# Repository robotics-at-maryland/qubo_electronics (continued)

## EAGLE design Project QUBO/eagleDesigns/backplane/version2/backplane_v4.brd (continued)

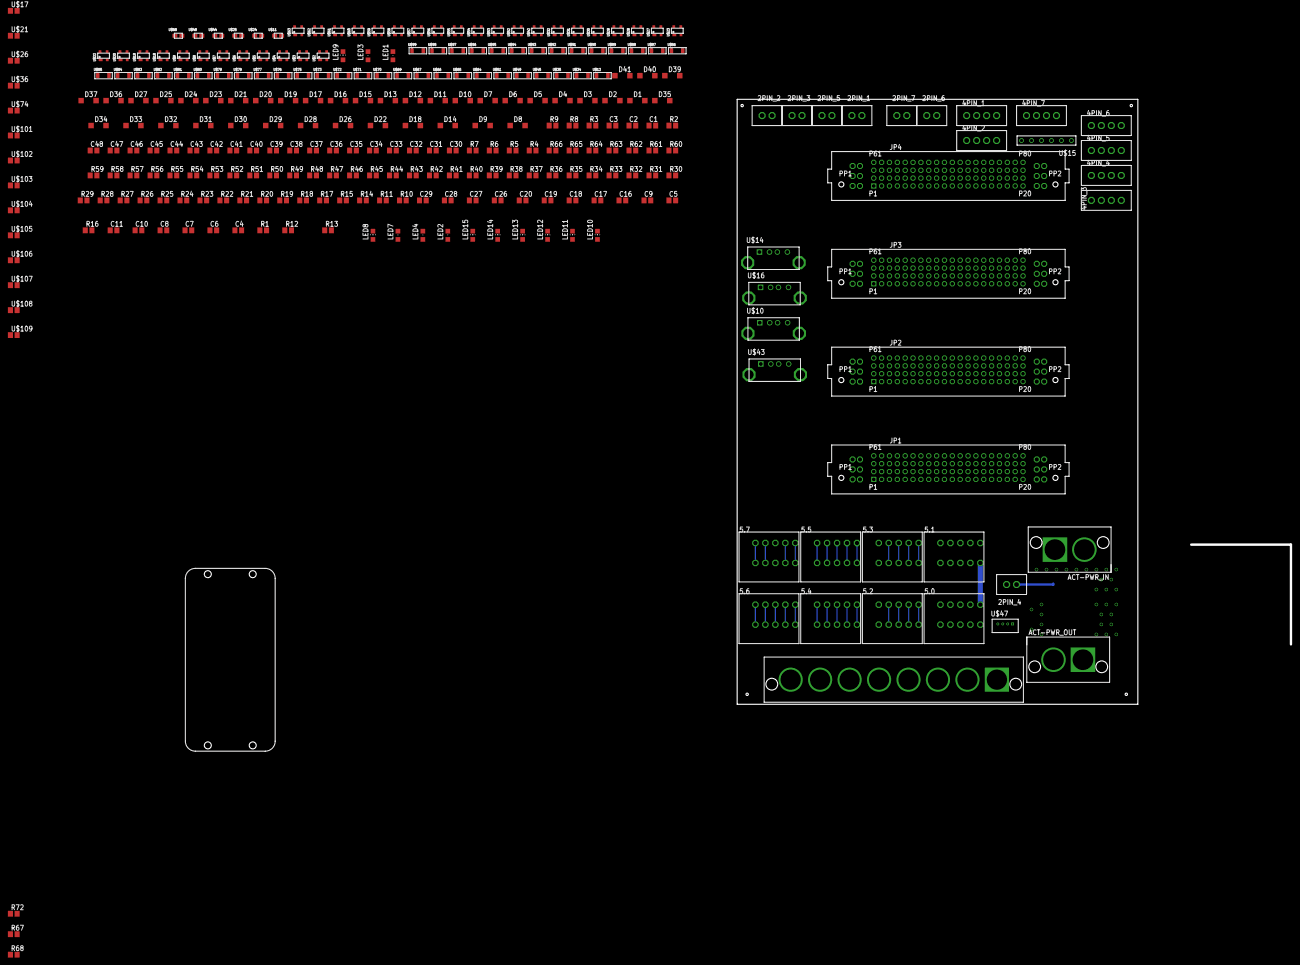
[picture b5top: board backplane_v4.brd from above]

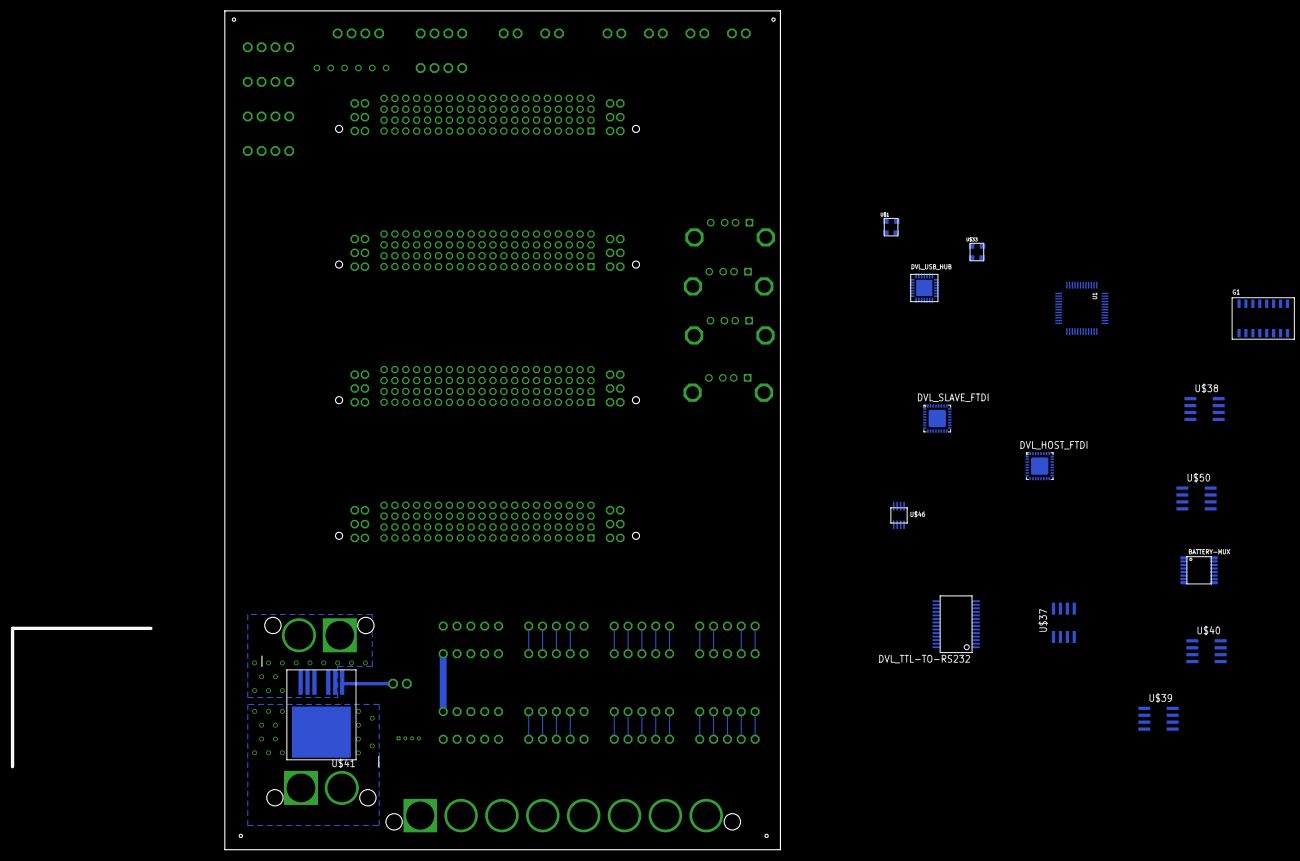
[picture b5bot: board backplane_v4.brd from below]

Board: 6 copper layers, 141.0 x 154.0 mm, 305 parts (16 on the bottom side), 197 nets.

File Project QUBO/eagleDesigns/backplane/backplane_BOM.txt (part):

Partlist exported from C:/Users/Ben/Documents/Dropbox/Documents/UMD/R@M/RAM Tran Electronics_2016/qubo_electronics.git/Project QUBO/eagleDesigns/backplane/version2/backplane_v4.sch at Tue, 2/7/2017 3:39 PM

Part             Value                     Device                    Package             Description                                                                               MF MPN     OC_FARNELL OC_NEWARK
2PIN_1           CPU_USB_HUB               KK254_VERT_2PIN22-29-2021 KK254_VERT_2PIN     KK® 254 Wire-to-Board Header, Vertical, with Friction Lock, 2 Circuits, Gold (Au) Plating                                
2PIN_2           CPU_USB_AHRS              KK254_VERT_2PIN22-29-2021 KK254_VERT_2PIN     KK® 254 Wire-to-Board Header, Vertical, with Friction Lock, 2 Circuits, Gold (Au) Plating                                
2PIN_3           CPU_USB_IMU               KK254_VERT_2PIN22-29-2021 KK254_VERT_2PIN     KK® 254 Wire-to-Board Header, Vertical, with Friction Lock, 2 Circuits, Gold (Au) Plating                                
2PIN_4           Magnetic Reed Switch plug KK254_VERT_2PIN22-29-2021 KK254_VERT_2PIN     KK® 254 Wire-to-Board Header, Vertical, with Friction Lock, 2 Circuits, Gold (Au) Plating                                
2PIN_5           CPU_USB_DVL               KK254_VERT_2PIN22-29-2021 KK254_VERT_2PIN     KK® 254 Wire-to-Board Header, Vertical, with Friction Lock, 2 Circuits, Gold (Au) Plating                                
2PIN_6           CPU_I2C_1                 KK254_VERT_2PIN22-29-2021 KK254_VERT_2PIN     KK® 254 Wire-to-Board Header, Vertical, with Friction Lock, 2 Circuits, Gold (Au) Plating                                
2PIN_7           CPU_CAN                   KK254_VERT_2PIN22-29-2021 KK254_VERT_2PIN     KK® 254 Wire-to-Board Header, Vertical, with Friction Lock, 2 Circuits, Gold (Au) Plating                                
4PIN_1           CPU_RS232_MCU             KK254_VERT_4PIN22-29-2041 KK254_VERT_4PIN     KK® 254 Wire-to-Board Header, Vertical, with Friction Lock, 4 Circuits, Gold (Au) Plating                                
4PIN_2           CPU_RS232_Flex            KK254_VERT_4PIN22-29-2041 KK254_VERT_4PIN     KK® 254 Wire-to-Board Header, Vertical, with Friction Lock, 4 Circuits, Gold (Au) Plating                                
4PIN_3           CPU_PWR1                  KK254_VERT_4PIN22-29-2041 KK254_VERT_4PIN     KK® 254 Wire-to-Board Header, Vertical, with Friction Lock, 4 Circuits, Gold (Au) Plating                                
4PIN_4           CPU_PWR2                  KK254_VERT_4PIN22-29-2041 KK254_VERT_4PIN     KK® 254 Wire-to-Board Header, Vertical, with Friction Lock, 4 Circuits, Gold (Au) Plating                                
4PIN_5           CPU_GND1                  KK254_VERT_4PIN22-29-2041 KK254_VERT_4PIN     KK® 254 Wire-to-Board Header, Vertical, with Friction Lock, 4 Circuits, Gold (Au) Plating                                
4PIN_6           CPU_GND2                  KK254_VERT_4PIN22-29-2041 KK254_VERT_4PIN     KK® 254 Wire-to-Board Header, Vertical, with Friction Lock, 4 Circuits, Gold (Au) Plating                                
4PIN_7           CPU_SPI                   KK254_VERT_4PIN22-29-2041 KK254_VERT_4PIN     KK® 254 Wire-to-Board Header, Vertical, with Friction Lock, 4 Circuits, Gold (Au) Plating                                
5.0              M250_5PIN                 M250_5PIN                 M205_5PIN           5-pin Eurostyle Terminal Block                                                                                           
5.1              M250_5PIN                 M250_5PIN                 M205_5PIN           5-pin Eurostyle Terminal Block                                                                                           
5.2              M250_5PIN                 M250_5PIN                 M205_5PIN           5-pin Eurostyle Terminal Block                                                                                           
5.3              M250_5PIN                 M250_5PIN                 M205_5PIN           5-pin Eurostyle Terminal Block                                                                                           
5.4              M250_5PIN                 M250_5PIN                 M205_5PIN           5-pin Eurostyle Terminal Block                                                                                           
5.5              M250_5PIN                 M250_5PIN                 M205_5PIN           5-pin Eurostyle Terminal Block                                                                                           
5.6              M250_5PIN                 M250_5PIN                 M205_5PIN           5-pin Eurostyle Terminal Block                                                                                           
5.7              M250_5PIN                 M250_5PIN                 M205_5PIN           5-pin Eurostyle Terminal Block                                                                                           
ACT-PWR_IN       SUPERSABRE_2CIRCUIT       SUPERSABRE_2CIRCUIT       SUPERSABRE_2CIRCUIT Molex SuperSabre                                                                                                         
ACT-PWR_OUT      SUPERSABRE_2CIRCUIT       SUPERSABRE_2CIRCUIT       SUPERSABRE_2CIRCUIT Molex SuperSabre                                                                                                         
BATTERY-MUX      PCA9546APW                PCA9546APW                TSSOP16             NXP 1:4 I2C Multiplexer                                                                                                  
C1               22p                       C-USC0805                 C0805               CAPACITOR, American symbol                                                                                               
C2               22p                       C-USC0805                 C0805               CAPACITOR, American symbol                                                                                               
C3               22p                       C-USC0805                 C0805               CAPACITOR, American symbol                                                                                               
C4               100n                      C-USC0805                 C0805               CAPACITOR, American symbol                                                                                               
C5               4.7u                      C-USC0805                 C0805               CAPACITOR, American symbol                                                                                               
C6               100n                      C-USC0805                 C0805               CAPACITOR, American symbol                                                                                               
C7               100n                      C-USC0805                 C0805               CAPACITOR, American symbol                                                                                               
C8               100n                      C-USC0805                 C0805               CAPACITOR, American symbol                                                                                               
C9               4.7u                      C-USC0805                 C0805               CAPACITOR, American symbol                                                                                               
C10              100n                      C-USC0805                 C0805               CAPACITOR, American symbol                                                                                               
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
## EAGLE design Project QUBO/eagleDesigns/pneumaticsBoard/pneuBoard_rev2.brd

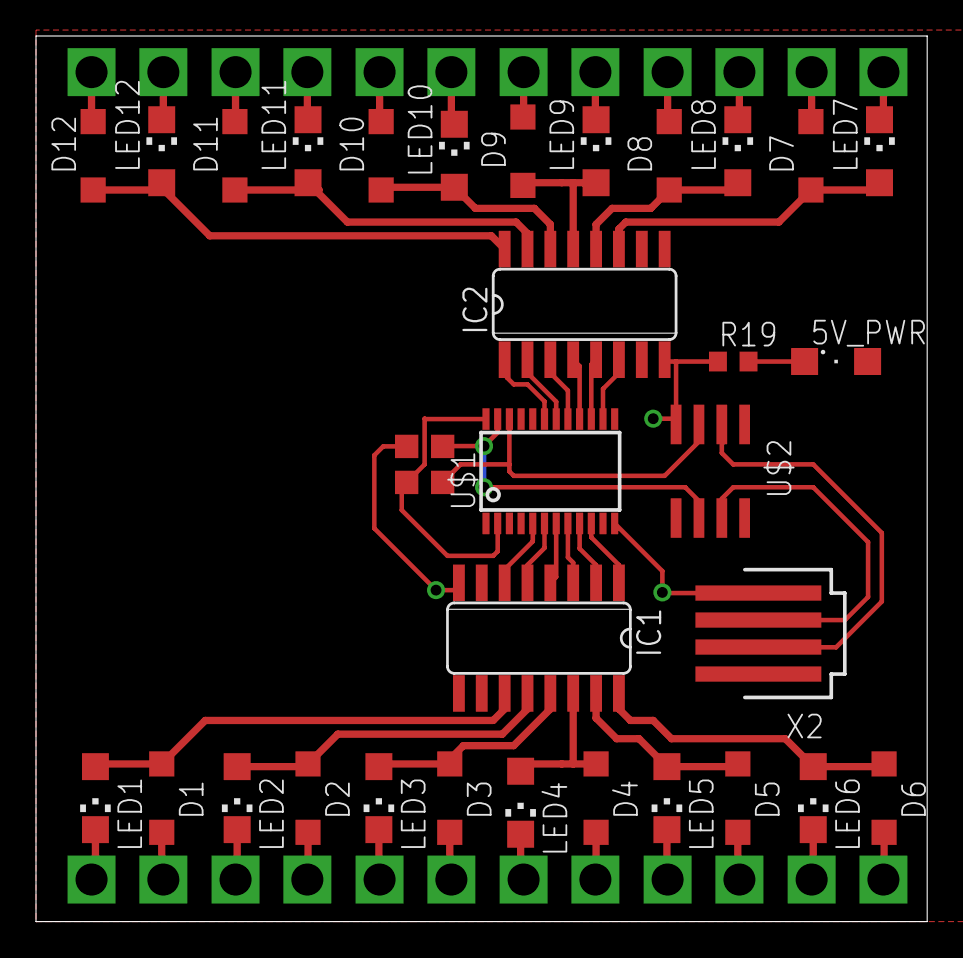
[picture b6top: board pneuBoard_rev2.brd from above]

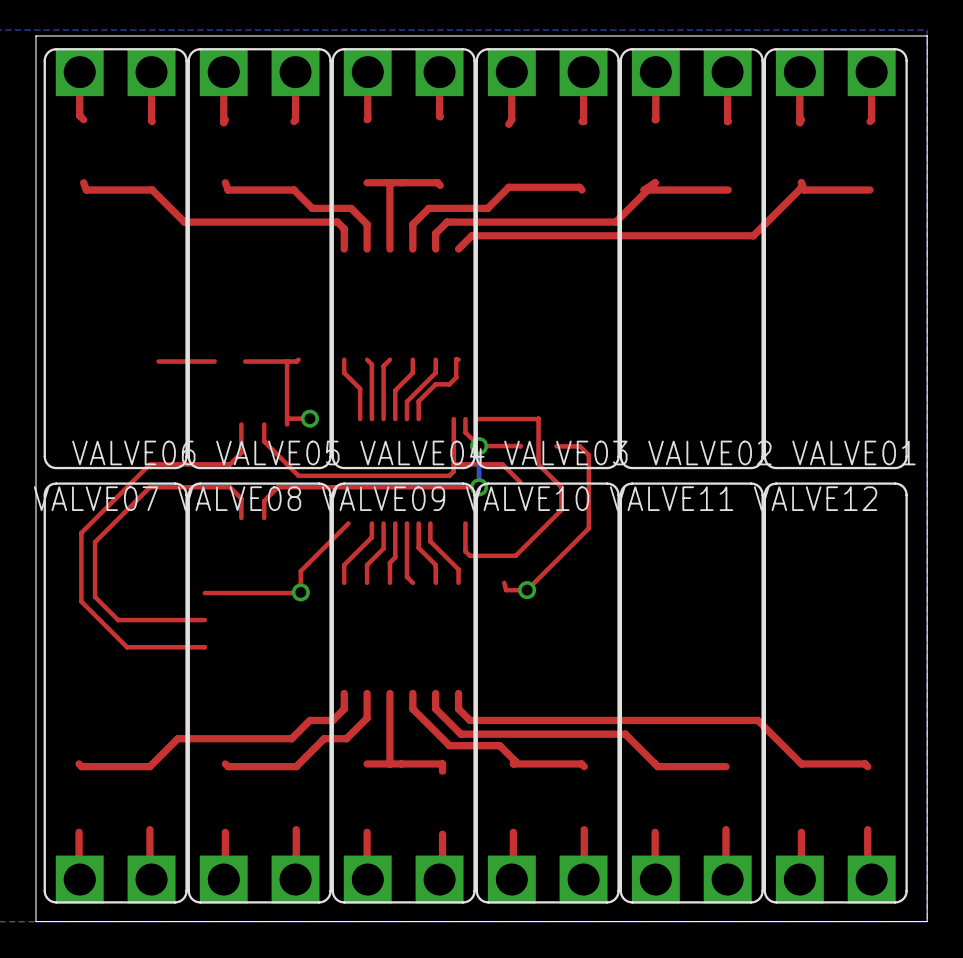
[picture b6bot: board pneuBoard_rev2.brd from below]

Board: 2 copper layers, 49.5 x 49.2 mm, 44 parts (12 on the bottom side), 43 nets.

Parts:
5V_PWR: SML1206
D1, D2, D3, D4, D5, D6, D7, D8, D9, D10, D11, D12: SOD123
IC1, IC2: ULN2001AD; SO16
LED1, LED2, LED3, LED4, LED5, LED6, LED7, LED8, LED9, LED10, LED11, LED12: CHIPLED_1206
R19: 1k; R0603
U$1: PCF8575C; PW_R-PDSO-G24
U$2: P82B715; SO8
U$3: MS5837-30BA
VALVE01, VALVE02, VALVE03, VALVE04, VALVE05, VALVE06, VALVE07, VALVE08, VALVE09, VALVE10, VALVE11, VALVE12: X-5-XX-L-F; X-SERIES
X2: 87438-04

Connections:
5V: 5V_PWR.A, IC1.9, IC2.9, U$1.2, U$1.3, U$1.21, U$1.24, U$2.8, U$3.2, X2.1
5V_LED: 5V_PWR.C, R19.2
GND: D1.A, D2.A, D3.A, D4.A, D5.A, D6.A, D7.A, D8.A, D9.A, D10.A, D11.A, D12.A, IC1.8, IC2.8, R19.1, U$1.12, U$2.4, U$3.1, VALVE01.P2, VALVE02.P2, VALVE03.P2, VALVE04.P2, VALVE05.P2, VALVE06.P2, VALVE07.P2, VALVE08.P2, VALVE09.P2, VALVE10.P2, VALVE11.P2, VALVE12.P2, X2.4
unnamed: LED1.C, VALVE01.P1
unnamed: LED3.C, VALVE03.P1
unnamed: LED4.C, VALVE04.P1
unnamed: LED5.C, VALVE05.P1
unnamed: LED6.C, VALVE06.P1
unnamed: LED9.C, VALVE09.P1
unnamed: LED2.C, VALVE02.P1
unnamed: LED8.C, VALVE08.P1
unnamed: LED7.C, VALVE07.P1
unnamed: LED10.C, VALVE10.P1
unnamed: LED11.C, VALVE11.P1
unnamed: LED12.C, VALVE12.P1
P01: IC1.6, U$1.5
P01_BUF: D1.C, IC1.11, LED1.A
P02: IC1.5, U$1.6
P02_BUF: D2.C, IC1.12, LED2.A
P03: IC1.4, U$1.7
P03_BUF: D3.C, IC1.13, LED3.A
P04: IC1.3, U$1.8
P04_BUF: D4.C, IC1.14, LED4.A
P05: IC1.2, U$1.9
P05_BUF: D5.C, IC1.15, LED5.A
P06: IC1.1, U$1.10
P06_BUF: D6.C, IC1.16, LED6.A
P11: IC2.6, U$1.14
P11_BUF: D7.C, IC2.11, LED7.A
P12: IC2.5, U$1.15
P12_BUF: D8.C, IC2.12, LED8.A
P13: IC2.4, U$1.16
P13_BUF: D9.C, IC2.13, LED9.A
P14: IC2.3, U$1.17
P14_BUF: D10.C, IC2.14, LED10.A
P15: IC2.2, U$1.18
P15_BUF: D11.C, IC2.15, LED11.A
P16: IC2.1, U$1.19
P16_BUF: D12.C, IC2.16, LED12.A
SCL: U$1.22, U$2.3, U$3.3
SCL_BUF: U$2.2, X2.2
SDA: U$1.23, U$2.6, U$3.4
SDA_BUF: U$2.7, X2.3

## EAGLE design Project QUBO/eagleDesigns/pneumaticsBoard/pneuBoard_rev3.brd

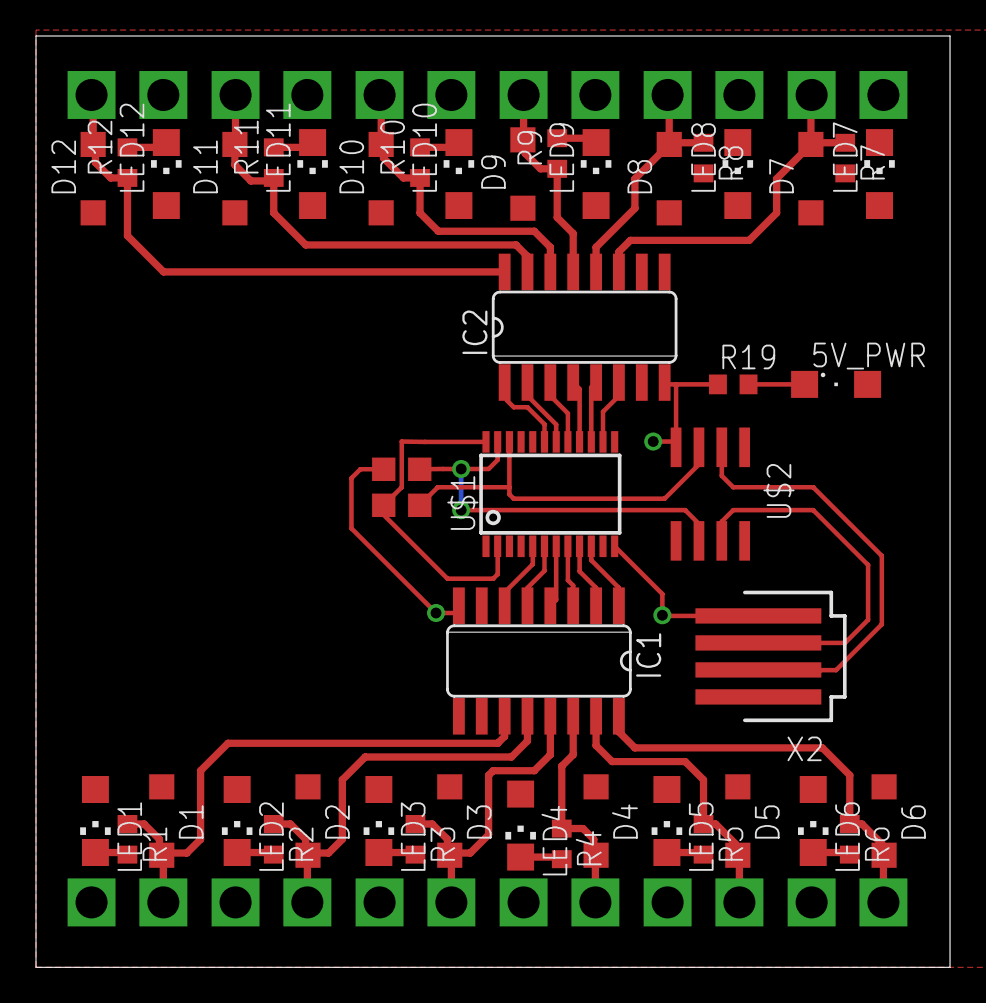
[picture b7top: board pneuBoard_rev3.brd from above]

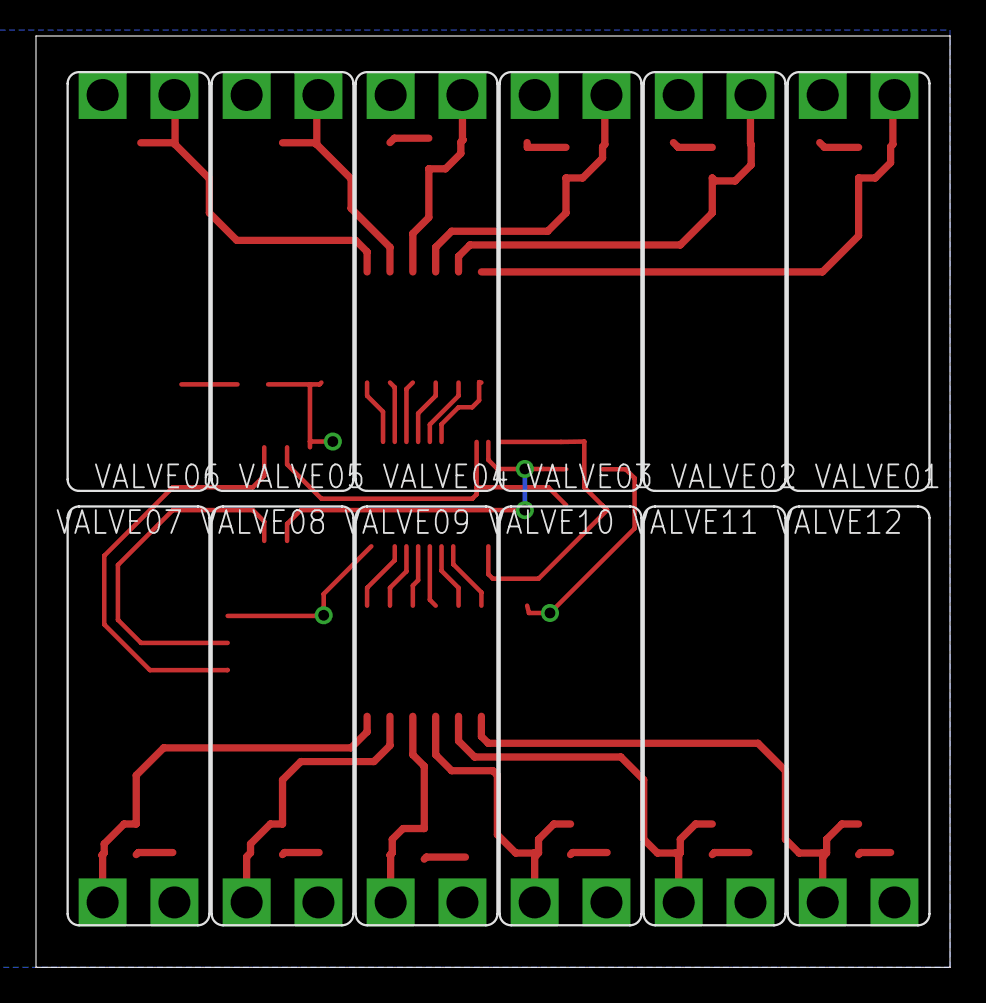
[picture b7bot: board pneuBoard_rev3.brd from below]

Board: 2 copper layers, 50.8 x 51.7 mm, 56 parts (12 on the bottom side), 43 nets.

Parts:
5V_PWR: SML1206
D1, D2, D3, D4, D5, D6, D7, D8, D9, D10, D11, D12: SOD123
IC1, IC2: ULN2001AD; SO16
LED1, LED2, LED3, LED4, LED5, LED6, LED7, LED8, LED9, LED10, LED11, LED12: CHIPLED_1206
R1, R2, R3, R4, R5, R6, R7, R8, R9, R10, R11, R12: R0603
R19: 1k; R0603
U$1: PCF8575C; PW_R-PDSO-G24
U$2: P82B715; SO8
U$3: MS5837-30BA
VALVE01, VALVE02, VALVE03, VALVE04, VALVE05, VALVE06, VALVE07, VALVE08, VALVE09, VALVE10, VALVE11, VALVE12: X-5-XX-L-F; X-SERIES
X2: 87438-04

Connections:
5V: 5V_PWR.A, D1.C, D2.C, D3.C, D4.C, D5.C, D6.C, D7.C, D8.C, D9.C, D10.C, D11.C, D12.C, IC1.9, IC2.9, LED1.A, LED2.A, LED3.A, LED4.A, LED5.A, LED6.A, LED7.A, LED8.A, LED9.A, LED10.A, LED11.A, LED12.A, U$1.2, U$1.3, U$1.21, U$1.24, U$2.8, U$3.2, VALVE01.P1, VALVE02.P1, VALVE03.P1, VALVE04.P1, VALVE05.P1, VALVE06.P1, VALVE07.P1, VALVE08.P1, VALVE09.P1, VALVE10.P1, VALVE11.P1, VALVE12.P1, X2.1
5V_LED: 5V_PWR.C, R19.2
GND: IC1.8, IC2.8, R19.1, U$1.12, U$2.4, U$3.1, X2.4
unnamed: LED4.C, R4.2
unnamed: LED5.C, R5.2
unnamed: LED6.C, R6.2
unnamed: LED1.C, R1.2
unnamed: LED2.C, R2.2
unnamed: LED3.C, R3.2
unnamed: LED7.C, R7.2
unnamed: LED8.C, R8.2
unnamed: LED9.C, R9.2
unnamed: LED10.C, R10.2
unnamed: LED11.C, R11.2
unnamed: LED12.C, R12.2
P01: IC1.6, U$1.5
P01_BUF: D1.A, IC1.11, R1.1, VALVE01.P2
P02: IC1.5, U$1.6
P02_BUF: D2.A, IC1.12, R2.1, VALVE02.P2
P03: IC1.4, U$1.7
P03_BUF: D3.A, IC1.13, R3.1, VALVE03.P2
P04: IC1.3, U$1.8
P04_BUF: D4.A, IC1.14, R4.1, VALVE04.P2
P05: IC1.2, U$1.9
P05_BUF: D5.A, IC1.15, R5.1, VALVE05.P2
P06: IC1.1, U$1.10
P06_BUF: D6.A, IC1.16, R6.1, VALVE06.P2
P11: IC2.6, U$1.14
P11_BUF: D7.A, IC2.11, R7.1, VALVE07.P2
P12: IC2.5, U$1.15
P12_BUF: D8.A, IC2.12, R8.1, VALVE08.P2
P13: IC2.4, U$1.16
P13_BUF: D9.A, IC2.13, R9.1, VALVE09.P2
P14: IC2.3, U$1.17
P14_BUF: D10.A, IC2.14, R10.1, VALVE10.P2
P15: IC2.2, U$1.18
P15_BUF: D11.A, IC2.15, R11.1, VALVE11.P2
P16: IC2.1, U$1.19
P16_BUF: D12.A, IC2.16, R12.1, VALVE12.P2
SCL: U$1.22, U$2.3, U$3.3
SCL_BUF: U$2.2, X2.2
SDA: U$1.23, U$2.6, U$3.4
SDA_BUF: U$2.7, X2.3

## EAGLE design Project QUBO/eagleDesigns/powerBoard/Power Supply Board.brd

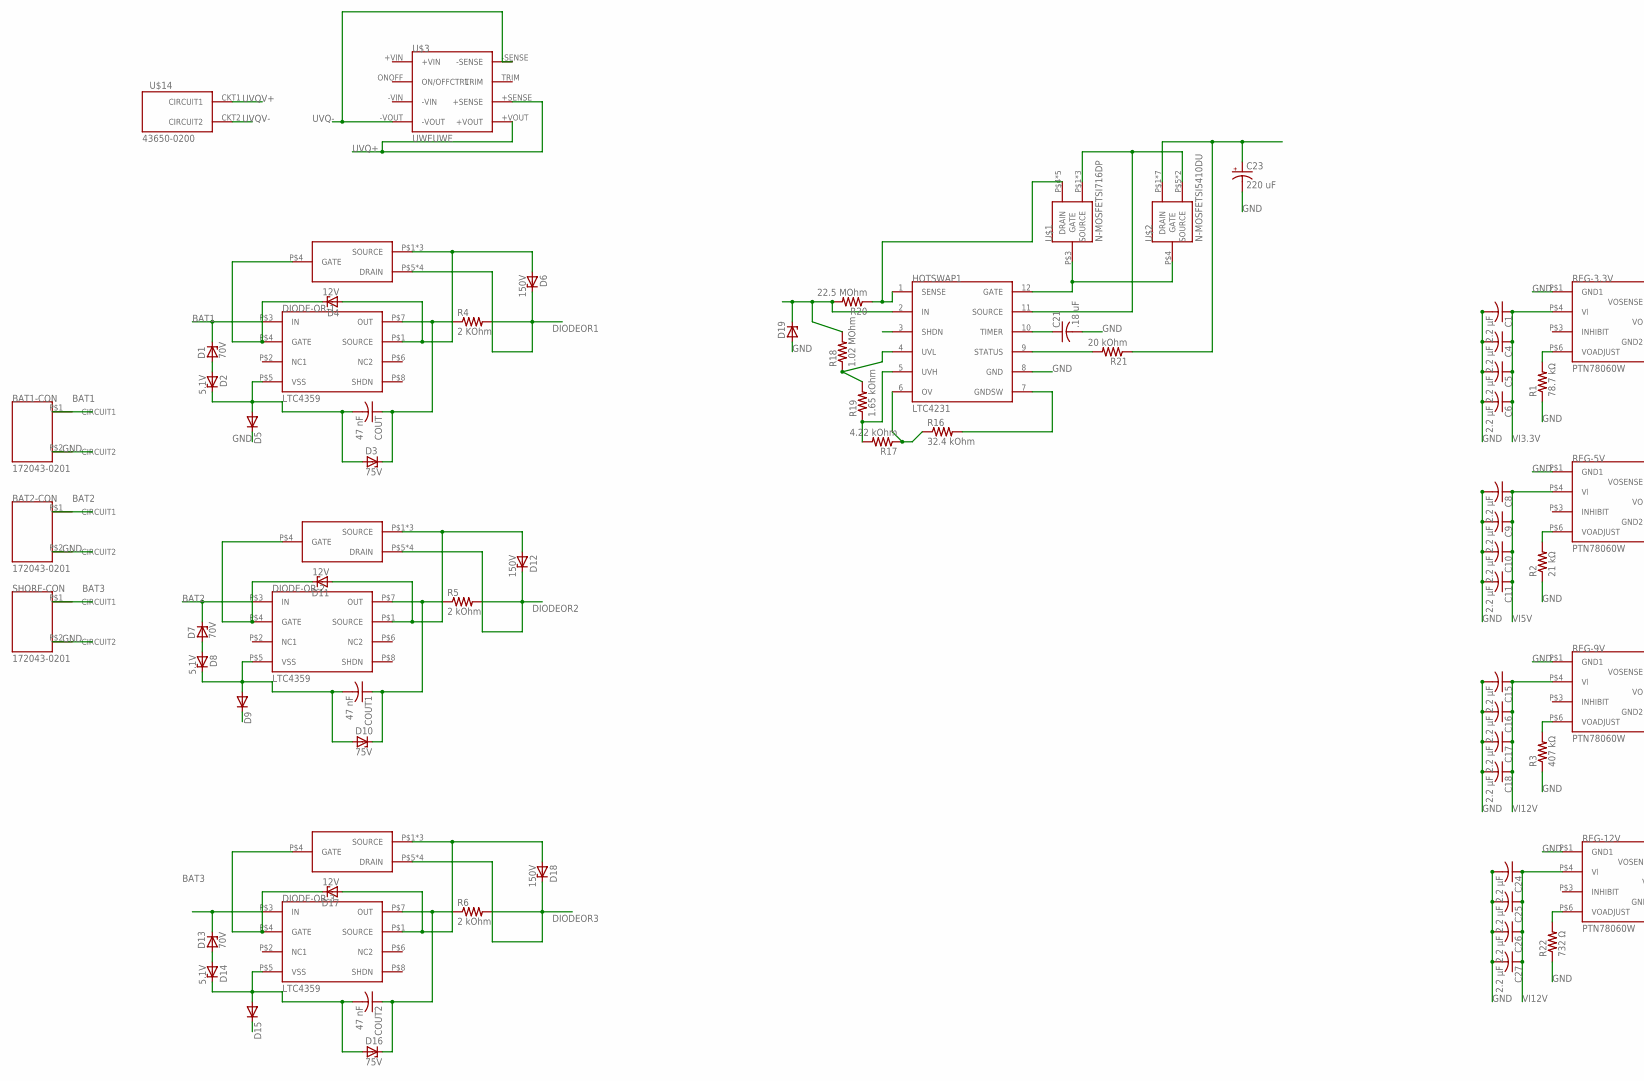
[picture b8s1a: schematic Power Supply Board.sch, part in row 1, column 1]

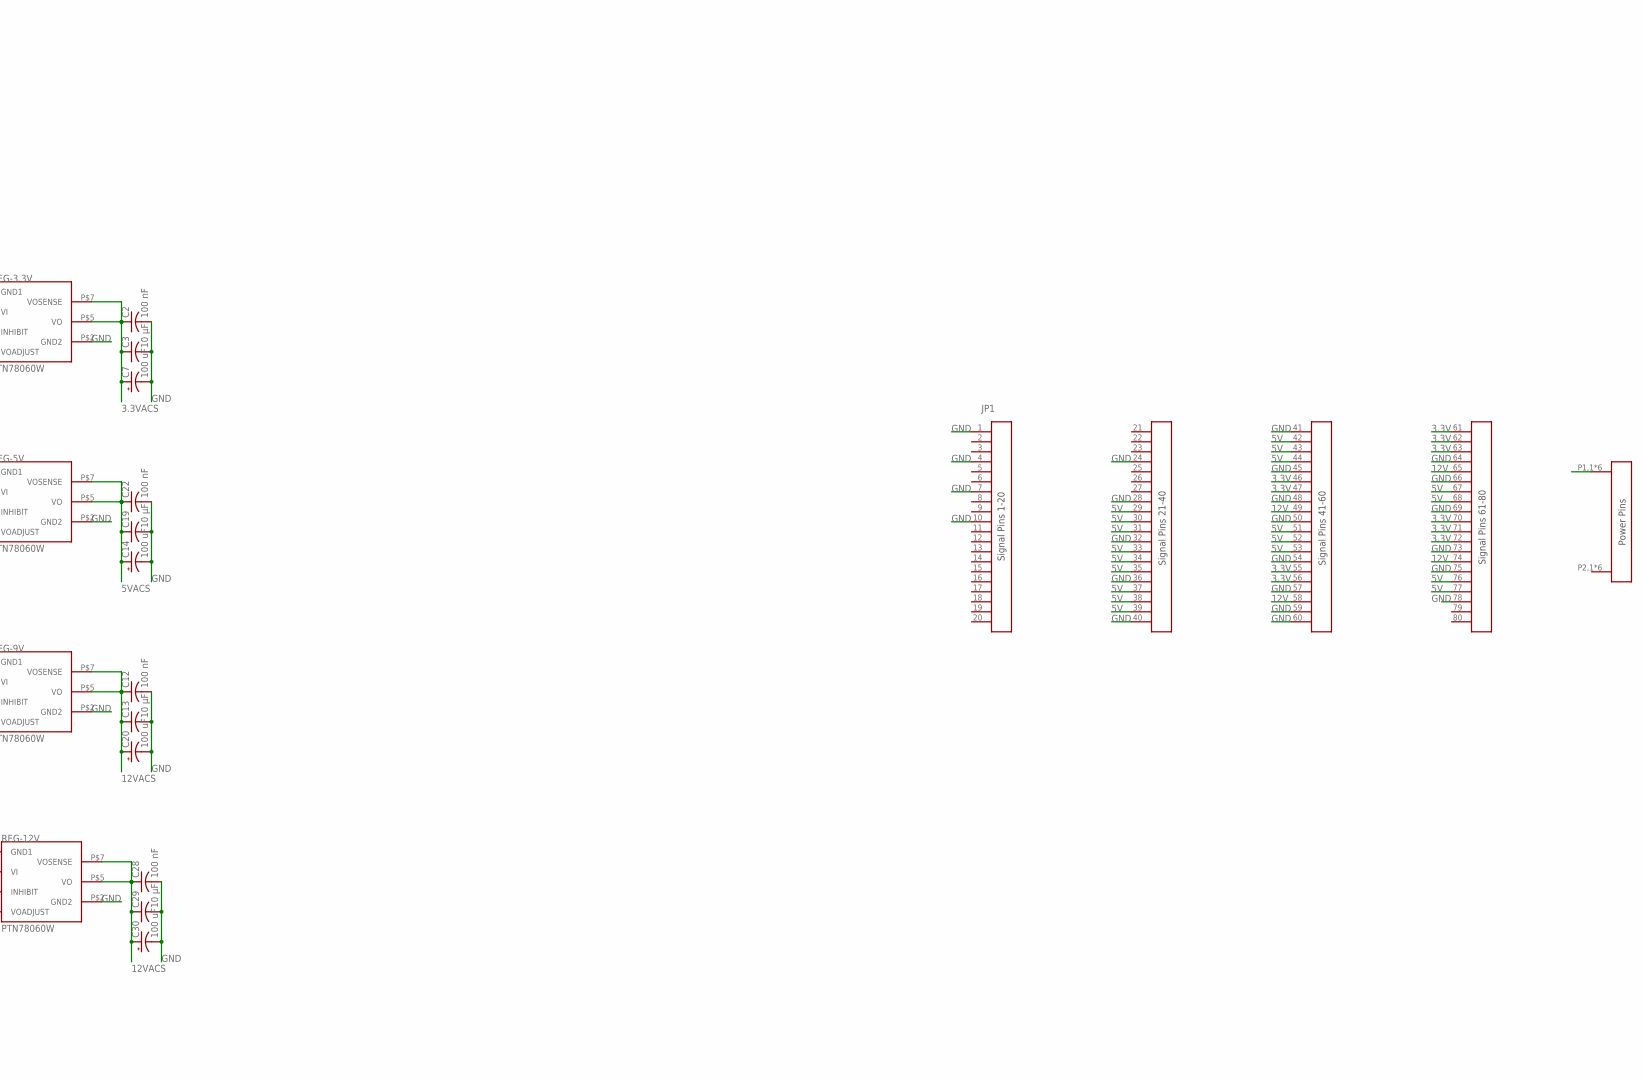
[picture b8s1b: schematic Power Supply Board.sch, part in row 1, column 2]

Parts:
BAT1-CON, BAT2-CON: 172043-0201
C1, C4, C5, C6, C8, C9, C10, C11, C15, C16, C17, C18, C24, C25, C26, C27: 2.2 µF; C1206
C2, C12, C22, C28: 100 nF; C0603
C3, C13, C19, C29: 10 µF; C0805
C7, C14, C20, C30: 100 uF; PANASONIC_D
C21: .18 uF; C0603
C23: 220 uF; PANASONIC_G
COUT, COUT1, COUT2: 47 nF; C0603
D1, D7, D13: 70V; C1702-15
D2, D8, D14: 5.1V; C1702-15
D3, D10, D16: 75V; TO236
D4, D11, D17: 12V; SMB
D5, D9, D15: DIODE-SOD123; SOD123
D6, D12, D18: 150V; SMB
D19: ZENER-DIODESMAJ; SMAJ
DIODE-OR-1, DIODE-OR-2, DIODE-OR-3: LTC4359
HOTSWAP1: LTC4231
JP1: MPSC-01-80MPSC-RA-LC; MPSC-01-80
R1: 78.7 kΩ; R0603
R2: 21 kΩ; R0603
R3: 407 kΩ; R0603
R4: 2 KOhm; R0603
R5, R6: 2 kOhm; R0603
R16: 32.4 kOhm; R0603
R17: 4.22 kOhm; R0603
R18: 1.02 MOhm; R0603
R19: 1.65 kOhm; R0603
R20: 22.5 MOhm; R0603
R21: 20 kOhm; R0603
R22: 732 Ω; R0603
REG-3.3V, REG-5V, REG-9V, REG-12V: PTN78060W
SHORE-CON: 172043-0201
U$1: N-MOSFETSI716DP; SI7164DP
U$2: N-MOSFETSI5410DU; SI5410DU
U$3: UWEUWE; UWE
U$5, U$6, U$18: CSD19537Q3
U$14: 43650-0200

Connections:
3.3V: JP1.46, JP1.47, JP1.55, JP1.56, JP1.61, JP1.62, JP1.63, JP1.70, JP1.71, JP1.72
3.3VACS: C2.1, C3.1, C7.+, REG-3.3V.P$5 (VO), REG-3.3V.P$7 (VOSENSE)
5V: JP1.29, JP1.30, JP1.31, JP1.33, JP1.34, JP1.35, JP1.37, JP1.38, JP1.39, JP1.42, JP1.43, JP1.44, JP1.51, JP1.52, JP1.53, JP1.67, JP1.68, JP1.76, JP1.77
5VACS: C14.+, C19.1, C22.1, REG-5V.P$5 (VO), REG-5V.P$7 (VOSENSE)
12V: JP1.49, JP1.58, JP1.65, JP1.74
12VACS: C12.1, C13.1, C20.+, C28.1, C29.1, C30.+, REG-9V.P$5 (VO), REG-9V.P$7 (VOSENSE), REG-12V.P$5 (VO), REG-12V.P$7 (VOSENSE)
BAT1: BAT1-CON.P$1 (CIRCUIT1), D1.C, DIODE-OR-1.P$3 (IN)
BAT2: BAT2-CON.P$1 (CIRCUIT1), D7.C, DIODE-OR-2.P$3 (IN)
BAT3: D13.C, DIODE-OR-3.P$3 (IN), SHORE-CON.P$1 (CIRCUIT1)
DIODEOR1: D6.C, R4.2, U$18.P$5 (DRAIN), U$18.P$6 (DRAIN), U$18.P$7 (DRAIN), U$18.P$8 (DRAIN)
DIODEOR2: D12.C, R5.2, U$5.P$5 (DRAIN), U$5.P$6 (DRAIN), U$5.P$7 (DRAIN), U$5.P$8 (DRAIN)
DIODEOR3: D18.C, R6.2, U$6.P$5 (DRAIN), U$6.P$6 (DRAIN), U$6.P$7 (DRAIN), U$6.P$8 (DRAIN)
GATE1: D4.C, DIODE-OR-1.P$4 (GATE), U$18.P$4 (GATE)
GATE2: D17.C, DIODE-OR-3.P$4 (GATE), U$6.P$4 (GATE)
GATE7: D11.C, DIODE-OR-2.P$4 (GATE), U$5.P$4 (GATE)
GND: BAT1-CON.P$2 (CIRCUIT2), BAT2-CON.P$2 (CIRCUIT2), C1.2, C2.2, C3.2, C4.2, C5.2, C6.2, C7.-, C8.2, C9.2, C10.2, C11.2, C12.2, C13.2, C14.-, C15.2, C16.2, C17.2, C18.2, C19.2, C20.-, C21.2, C22.2, C23.-, C24.2, C25.2, C26.2, C27.2, C28.2, C29.2, C30.-, D5.C, D9.C, D19.P$2 (A), HOTSWAP1.8 (GND), JP1.1, JP1.4, JP1.7, JP1.10, JP1.24, JP1.28, JP1.32, JP1.36, JP1.40, JP1.41, JP1.45, JP1.48, JP1.50, JP1.54, JP1.57, JP1.59, JP1.60, JP1.64, JP1.66, JP1.69, JP1.73, JP1.75, JP1.78, R1.1, R2.1, R3.1, R22.1, REG-3.3V.P$1 (GND1), REG-3.3V.P$2 (GND2), REG-5V.P$1 (GND1), REG-5V.P$2 (GND2), REG-9V.P$1 (GND1), REG-9V.P$2 (GND2), REG-12V.P$1 (GND1), REG-12V.P$2 (GND2), SHORE-CON.P$2 (CIRCUIT2)
GND1: D15.C
unnamed: JP1.P1,1 (POWER1), JP1.P1,2 (POWER1), JP1.P1,3 (POWER1), JP1.P1,4 (POWER1), JP1.P1,5 (POWER1), JP1.P1,6 (POWER1)
unnamed: R2.2, REG-5V.P$6 (VOADJUST)
unnamed: R1.2, REG-3.3V.P$6 (VOADJUST)
unnamed: R3.2, REG-9V.P$6 (VOADJUST)
unnamed: D1.A, D2.A
unnamed: COUT.1, D3.C, DIODE-OR-1.P$7 (OUT), R4.1
unnamed: COUT.2, D2.C, D3.A, D5.A, DIODE-OR-1.P$5 (VSS)
unnamed: D7.A, D8.A
unnamed: COUT1.2, D8.C, D9.A, D10.A, DIODE-OR-2.P$5 (VSS)
unnamed: COUT1.1, D10.C, DIODE-OR-2.P$7 (OUT), R5.1
unnamed: D13.A, D14.A
unnamed: COUT2.2, D14.C, D15.A, D16.A, DIODE-OR-3.P$5 (VSS)
unnamed: COUT2.1, D16.C, DIODE-OR-3.P$7 (OUT), R6.1
unnamed: C21.1, HOTSWAP1.10 (TIMER)
unnamed: HOTSWAP1.7 (GNDSW), R16.2
unnamed: HOTSWAP1.6 (OV), R16.1, R17.1
unnamed: HOTSWAP1.4 (UVL), R18.1, R19.2
unnamed: HOTSWAP1.5 (UVH), R17.2, R19.1
unnamed: HOTSWAP1.1 (SENSE), R20.1, U$1.P$4 (DRAIN), U$1.P$6 (DRAIN), U$1.P$7 (DRAIN), U$1.P$8 (DRAIN), U$1.P$9 (DRAIN)
unnamed: HOTSWAP1.12 (GATE), U$1.P$3 (GATE), U$2.P$4 (GATE)
unnamed: D19.P$1 (C), HOTSWAP1.2 (IN), R18.2, R20.2
unnamed: HOTSWAP1.11 (SOURCE), U$1.P$1 (SOURCE), U$1.P$2 (SOURCE), U$1.P$5 (SOURCE), U$2.P$5 (SOURCE), U$2.P$9 (SOURCE)
unnamed: C23.+, R21.1, U$2.P$1 (DRAIN), U$2.P$2 (DRAIN), U$2.P$3 (DRAIN), U$2.P$6 (DRAIN), U$2.P$7 (DRAIN), U$2.P$8 (DRAIN), U$2.P$10 (DRAIN)
unnamed: HOTSWAP1.9 (STATUS), R21.2
unnamed: R22.2, REG-12V.P$6 (VOADJUST)
SHDN-HOT-1: HOTSWAP1.3 (SHDN)
SOURCE1: D4.A, D6.A, DIODE-OR-1.P$1 (SOURCE), U$18.P$1 (SOURCE), U$18.P$2 (SOURCE), U$18.P$3 (SOURCE)
SOURCE2: D17.A, D18.A, DIODE-OR-3.P$1 (SOURCE), U$6.P$1 (SOURCE), U$6.P$2 (SOURCE), U$6.P$3 (SOURCE)
SOURCE7: D11.A, D12.A, DIODE-OR-2.P$1 (SOURCE), U$5.P$1 (SOURCE), U$5.P$2 (SOURCE), U$5.P$3 (SOURCE)
UVQ+: U$3.+SENSE, U$3.+VOUT
UVQ-: U$3.-SENSE, U$3.-VOUT
UVQV+: U$14.CKT1 (CIRCUIT1)
UVQV-: U$14.CKT2 (CIRCUIT2)
VI3.3V: C1.1, C4.1, C5.1, C6.1, REG-3.3V.P$4 (VI)
VI5V: C8.1, C9.1, C10.1, C11.1, REG-5V.P$4 (VI)
VI12V: C15.1, C16.1, C17.1, C18.1, C24.1, C25.1, C26.1, C27.1, REG-9V.P$4 (VI), REG-12V.P$4 (VI)

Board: 2 copper layers, 84 parts (0 on the bottom side), 49 nets, no tracks yet.
